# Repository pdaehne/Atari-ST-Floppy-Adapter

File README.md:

# Atari ST Floppy Adapter

This repository contains the KiCad project and Gerber files for an adapter that
converts the Atari ST external 14 pin floppy connector to a standard 34 pin IDC
box header. The 14 pin floppy connectors are out of production for a long time
and are extremely hard to get hold of and expensive nowadays. This adapter is a
cheap workaround.

This floppy adapter is designed to be used in combination with my
[DSUB-19 Adapter for the Atari DMA/Harddisk port](https://github.com/pdaehne/DSUB19-Adapter),
they fit nicely next to each other. I also tried not to block other connectors,
but I only have an Atari 1040 STF to check that, so your mileage might vary.
Please check the situation on your Atari before ordering the PCBs!

When you are still looking for a way to provide power to your external floppy
drive or Gotek floppy emulator, you might be interested in my
[Atari ST 5V Cartridge](https://github.com/pdaehne/Atari-ST-5V-Cartridge), which
utilizes the cartridge port of the Atari ST to provide 5V to external devices.

## Acknowlegements

This project is based on the
[work of Justin Davis](https://hackaday.io/project/181628-atari-st-floppy-drive-emulator-adapters)
who shared the information about the correct pins for the adapter in the comment
section of his project page, on the
[work of the user "Atarian Computing" on the Exxos Forum](https://www.exxoshost.co.uk/forum/viewtopic.php?t=956&sid=13cd7669f4fdfc9c40bdac74b315d1e2) who did the tedious task of measuring the
locations of the pins in the connector, and on the
[work of Michael Rath](https://forum.classic-computing.de/forum/index.php?thread/30190-sammelbestellung-atari-st-disketten-adapter/)
who had the idea with the configurable signals on pins 10 and 14 of the box
header. Michael sells his adapters on Ebay, so you might consider buying one
from him and supporting his work.

## Ordering the PCB

The subdirectory "gerber-files" contains a Zip file you can use to order the PCB
from PCB manufacturers like PCBWay or JLCPCB. Simply upload the Zip on their web
page. I recommend to order the standard PCB thickness of 1.6mm and HASL
finishing.

## Building the Adapter

### Bill of Materials

* __14x Solder Pins__.

  These pins are used to recreate the 14 pin floppy plug. They are Mill-Max
  4123-0-00-15-00-00-08-0. You can get these e.g. from DigiKey or Mouser.

* __1x 2x17 Pin Straight Male Box Header 2.54mm pitch__.

  Used to connect the flat ribbon cable to the adapter.

* __2x 1x3 Pin Headers 2.54mm pitch (optional)__.

  Used to select the signals that go to pins 10 and 14 of the box header. These
  are only needed when you want to be able to configure your adapter for
  different setups, otherwise you can simply bridge the connections on the PCB
  by soldering in a piece of wire.

* __2x Jumpers 2.54mm pitch (optional)__.

  Used to select the signals that go to pins 10 and 14 of the box header.

* __3x Self Adhesive Silicone Rubber Pads 5x2mm (optional)__.

  These are used to prevent the pins on the back of the adapter from scratching
  the case of your Atari ST. They must be quite small, 5mm diameter and a height
  of 2mm. You might be able to get these locally in a stationery shop or a
  hardware store, but I got mine from AliExpress.

### Soldering the Pins

Start with soldering the 14 pins/nails to the PCB. It is crucial that you solder
these pins straight to the PCB, otherwise they will not fit into the socket. I
recommend to use the actual floppy socket on your Atari ST or on an old external
floppy drive as a soldering aid. Stick the pins into the socket, and attach the
PCB to the pins, e.g. by using an adhesive like
[Blu Tack](https://en.wikipedia.org/wiki/Blu_Tack). Solder the pins to the PCB,
but be careful not to destroy your soldering aid by applying excessive heat or
by dropping solder.

I myself did only have the socket on my Atari ST, and I did not succeed to
solder the pins without removing the mainboard from the case - whenever I tried
to put the PCB on the pins I pushed the pins too far into the socket. Removing
the mainboard is quite a tedious task, but doing it this way is much easier and
prevents you from damaging your precious Atari ST case. But nevertheless, the
whole soldering process is quite finicky.

### Soldering the Box Header

Solder the box header to the PCB. Mind the orientation, the notch of the header
must face in the direction marked on the silk screen (downwards in the image
below in direction to the pins).

Before soldering the box header, there is an optional step that I recommend to
do. When you plan to use an original floppy cable from an IBM-compatible PC, you
might realize that these cables are frequently keyed with a missing pin. On the
box header it is the third pin from the left in the bottom row (see the images
below). On the floppy side, it is actually the second pin that is missing, so
you cannot install the cable in the wrong direction, but do not get confused -
on the adapter side, you have to remove the third pin! Removing the pin is
actually quite easy - simply use a pair of pliers to pull the pin out of the
socket. Again, please do triple-check that you remove the third pin from the
left on the row facing the notch (see the images below) - when you get this
wrong, you might get a non-working adapter!

Even when the cable that you plan to use to connect your floppy to the adapter
does not have this keying, I nevertheless recommend that you remove the pin,
because it is easy to do, and doing it after soldering the box header to the PCB
is nearly impossible.

To solder the box header to the PCB, I again recommend to use an adhesive like
Blu Tack to stick it to the PCB. I also recommend to stick the floppy cable into
the socket, because it happens easily that the plastic of the socket melts and
the pins start to move when you apply too much heat while soldering, and this
might ruin the whole adapter!

### Soldering the Pin Headers

Next step is to solder the two pin headers used to configure the signals on pins
10 and 14 of the box header. How to configure the adapter is explained more in
detail in the section [Using the Adapter](#using-the-adapter) below. Of course
using pin headers and jumpers is optional - when you do not need support for
multiple configurations, you can also simply solder pieces of wire to the PCB
to generate a fixed configuration. When soldering, make sure that you solder the
pin headers straight onto the PCB.

### Attaching the Silicone Rubber Pads

The final step is to stick the silicone rubber pads to the adapter. This step
of course is completly optional, but when you attach the adapter to your Atari
ST, the pins on the back get in contact with its case and might scratch it.
Simply sticking three rubber pads to the adapter as shown in the image below
will prevent that from happening.

## Using the Adapter

Carefully push the adapter into the 14 pin floppy socket. Use the cable to
connect your external floppies to the adapter.

Before you can use the adapter, you have to configure it correctly for your
specific setup. To understand this process, we have to dive into the theory of
how floppies and floppy cables actually work. This is a simplified overview just
for configuring the adapter, and I will leave out many details which are not
important for that task.

On Atari ST machines as well as IBM-compatible PCs, you can attach up to two
floppy drives, called drive "A" and drive "B". On the floppy connectors and the
floppy cables, there are two signal lines which tell the floppies to which one
of both the computer is currently talking to. These signals are called "Drive
Select 0" (short "DS0") for drive A, and "Drive Select 1" (short "DS1") for
drive B.

On the Atari ST, you have to configure the drives whether they respond to DS0 or
DS1. There are little jumpers on the floppy drives that you have to set
accordingly.

On PCs, a much simpler solution is used. PC floppy drives are generally
configured to respond to DS1, and it is usually not possible to change this
configration without using a soldering iron. There is a twist on PC floppy
cables that exchanges the signals DS0 and DS1 (see image below). When you
connect a PC floppy to a connector after the twist, it becomes drive A. When you
connect it to a connector before the twist, it becomes drive B.

These differences between Atari ST and PC floppy drives and cables lead to a
lot of confusion when connecting floppies or floppy emulators like Gotek drives.
This is complicated even more by the fact that there are Atari STs without
internal drives (e.g. 520 ST) and with internal drives (e.g. 1040 STF). When you
have an Atari ST with an internal drive, you can only connect one external
drive. The DS0 signal line on the external connector internally is actually
connected to DS1, so DS0 and DS1 are the same signal. To connect two external
drives to an Atari 1040 STF, you have to disconnect the internal drive and you
have to modify the mainboard to provide signal DS0 to the external connector.

So, after all that background information, let us get back to the configuration
of the adapter.

There are two pin headers with 3 pins, respectively.

The left one controls the signal on pin 10 of the box header. When you connect
the left and the center pin with a jumper, the "Motor" signal is connected to
pin 10. When you connect the center and the right pin, the "DS0" signal is
connected to pin 10. Whenever you are connecting a floppy using a _twisted_
cable, you have to use the "Motor" signal, otherwise you have to use the "DS0"
signal.

The right pin header controls the signal on pin 14 of the box header. When you
connect the left and the center pin with a jumper, the "DS1" signal is connected
to pin 14. When you connect the center and the right pin, the "DS0" signal is
connected to pin 14. Whenever you are connecting a floppy with an _untwisted_
cable, you can ignore this pin header, i.e. you do not have to set a jumper, it
does not matter. Otherwise, when using a _twisted_ cable, you control which
drive select signal gets sent to the floppy at the connector behind the twist.
When the floppy is configured as "DS0", you have to send the "DS0" signal, and
when the floppy is configured as "DS1", you have to send the "DS1" signal.

Let us have a look at some concrete scenarios. We will start with the simple
case, an Atari ST with an integrated floppy (A) and one single external floppy
(B):

* When you use a straight, untwisted cable:

  The external floppy (B) can be configured either for DS0 or DS1. Pin 10 must
  be configured as DS0, so on the left pin header, you have to connect the
  center and the right pin with a jumper. Pin 14 is not used, so leave the right
  pin header without a jumper.

  <picture>
    <source media="(prefers-color-scheme: dark)" srcset="images/straight_cable_one_floppy.dark.svg">
    
  </picture>

* When you use a twisted cable:

  The external floppy (B) must be configured for DS1. Pin 10 must be configured
  as Motor, so on the left pin header, you have to connect the left and the
  center pin with a jumper. Pin 14 must be configured as DS1, so on the right
  pin header, you have to connect the left and the center pin with a jumper.

  <picture>
    <source media="(prefers-color-scheme: dark)" srcset="images/twisted_cable_one_floppy.dark.svg">
    
  </picture>

Now, let us have a look at an Atari ST without an integrated floppy and two
external floppies (when you only attach a single external floppy, use the same
configuration, and simply leave drive B away):

* When you use a straight, untwisted cable:

  One floppy (A) must be configured for DS0, and the other floppy (B) must be
  configured for DS1. Pin 10 must be configured as DS0, so on the left pin
  header, you have to connect the center and the right pin with a jumper. Pin 14
  is not used, so leave the right pin header without a jumper.

  <picture>
    <source media="(prefers-color-scheme: dark)" srcset="images/straight_cable_two_floppies.dark.svg">
    
  </picture>

* When you use a twisted cable:

  Both floppies must be configured for DS1. The floppy after the twist becomes
  drive A, and the floppy before the twist becomes drive B. Pin 10 must be
  configured as Motor, so on the left pin header, you have to connect the left
  and the center pin with a jumper. Pin 14 must be configured as DS0, so on
  the right pin header, you have to connect the center and the right pin with a
  jumper.

  <picture>
    <source media="(prefers-color-scheme: dark)" srcset="images/twisted_cable_two_floppies.dark.svg">
    
  </picture>

> [!NOTE]
> When you use this adapter to connect actual floppy drives instead of Gotek
> emulators, you might notice that the motors of both floppy drives start to
> spin when you try to access any of the drives. This is actually correct and
> the expected behaviour!

> [!NOTE]
> Also notice that the Atari ST only boots from drive A. When your Atari ST has
> a built-in floppy, that floppy is drive A. You won't be able to boot from the
> external drive, unless you do a hardware mod to the machine.

## License

Atari ST Floppy Adapter (c) by Patrick Dähne

Atari ST Floppy Adapter is licensed under a
Creative Commons Attribution-NonCommercial-ShareAlike 4.0 International License.

You should have received a copy of the license along with this
work. If not, see <https://creativecommons.org/licenses/by-nc-sa/4.0/>.

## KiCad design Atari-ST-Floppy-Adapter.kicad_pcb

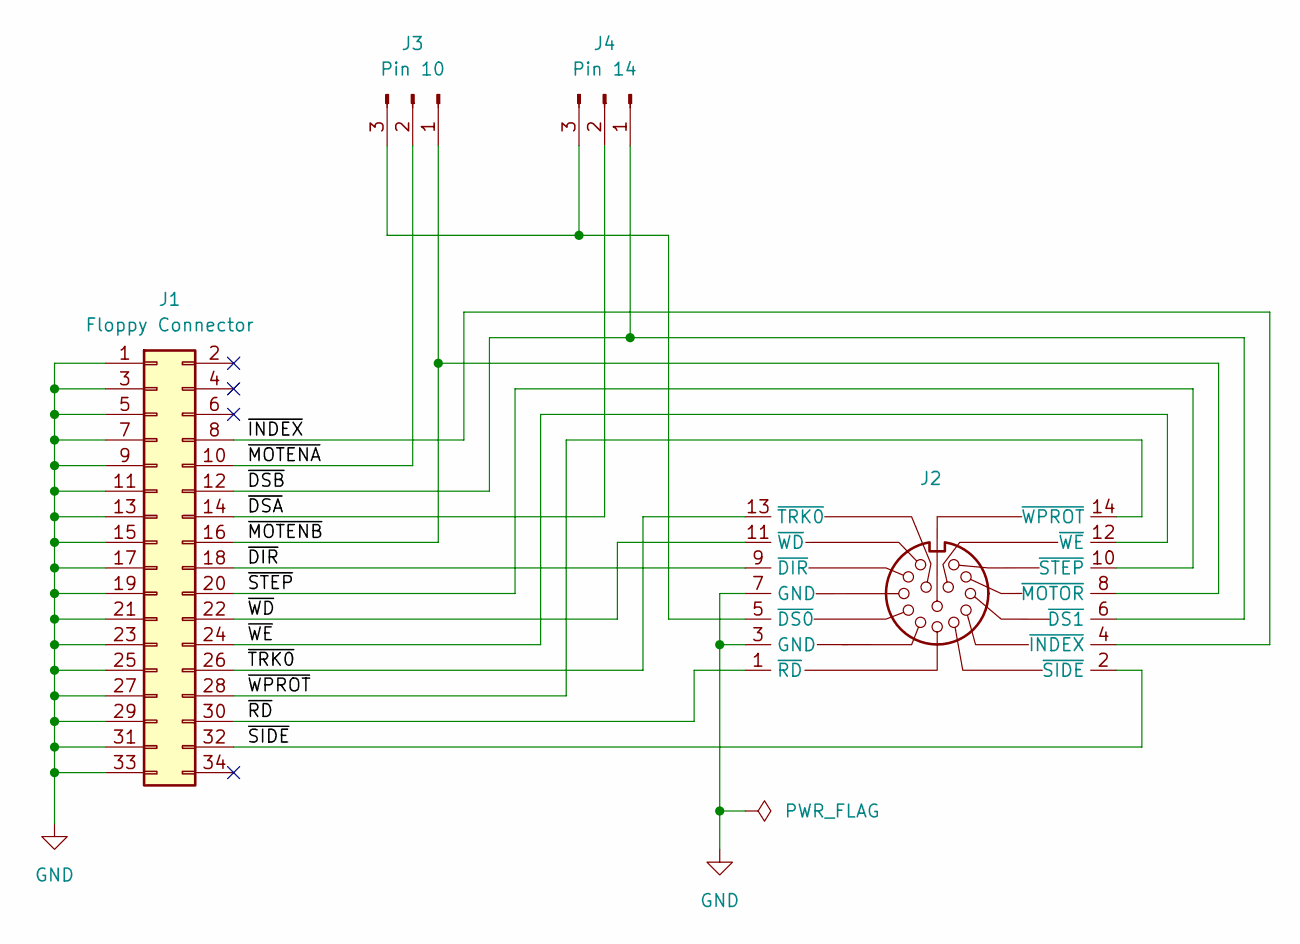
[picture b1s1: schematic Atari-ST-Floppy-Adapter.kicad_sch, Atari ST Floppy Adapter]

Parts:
J1: Floppy Connector; IDC-Header_2x17_P2.54mm_Vertical
J2: Floppy Connector
J3: Pin 10; PinHeader_1x03_P2.54mm_Vertical
J4: Pin 14; PinHeader_1x03_P2.54mm_Vertical

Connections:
/~DIR: J1.18, J2.9 (~DIR)
/~DSA: J1.14, J4.2
/~DSB: J1.12, J2.6 (~DS1), J4.1
/~INDEX: J1.8, J2.4 (~INDEX)
/~MOTENA: J1.10, J3.2
/~MOTENB: J1.16, J2.8 (~MOTOR), J3.1
/~RD: J1.30, J2.1 (~RD)
/~SIDE: J1.32, J2.2 (~SIDE)
/~STEP: J1.20, J2.10 (~STEP)
/~TRK0: J1.26, J2.13 (~TRK0)
/~WD: J1.22, J2.11 (~WD)
/~WE: J1.24, J2.12 (~WE)
/~WPROT: J1.28, J2.14 (~WPROT)
GND: J1.1, J1.3, J1.5, J1.7, J1.9, J1.11, J1.13, J1.15, J1.17, J1.19, J1.21, J1.23, J1.25, J1.27, J1.29, J1.31, J1.33, J2.3 (GND), J2.7 (GND)
unnamed: J2.5 (~DS0), J3.3, J4.3

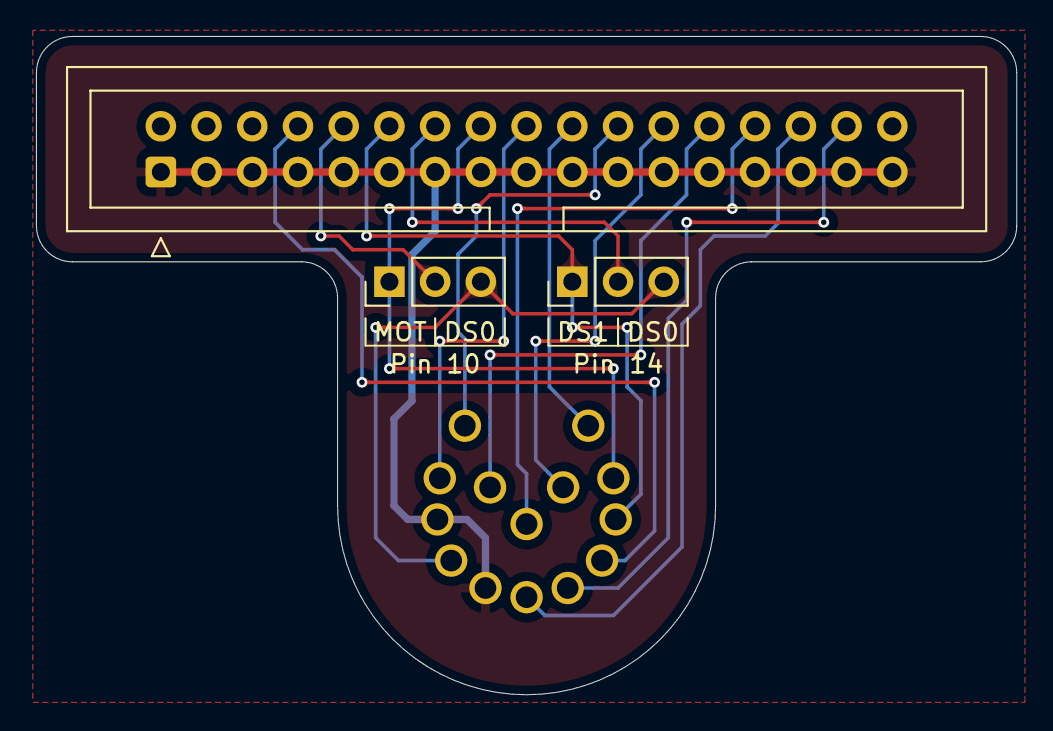
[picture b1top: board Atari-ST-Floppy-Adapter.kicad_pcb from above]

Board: 2 copper layers, 54.5 x 36.6 mm, 4 parts (1 on the bottom side), 15 nets.

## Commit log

2025-08-20 Initial check-in
2025-08-20 Fixed access rights
2025-08-20 Switched to sans-serif font
2025-08-20 Fixed missing pin number
2025-09-16 Made separate images for light and dark mode
2025-09-17 Made light images lighter
2025-12-03 Fixed typos and removed non-working URLs
2025-12-03 Fixed another typo
2025-12-03 Replaced one word
2025-12-11 Added reference to the Atari ST 5V Cartridge

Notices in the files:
Atari-ST-Floppy-Adapter.kicad_pcb:
Patrick Dähne CC BY-NC-SA 4.0
CC BY-NC-SA 4.0
